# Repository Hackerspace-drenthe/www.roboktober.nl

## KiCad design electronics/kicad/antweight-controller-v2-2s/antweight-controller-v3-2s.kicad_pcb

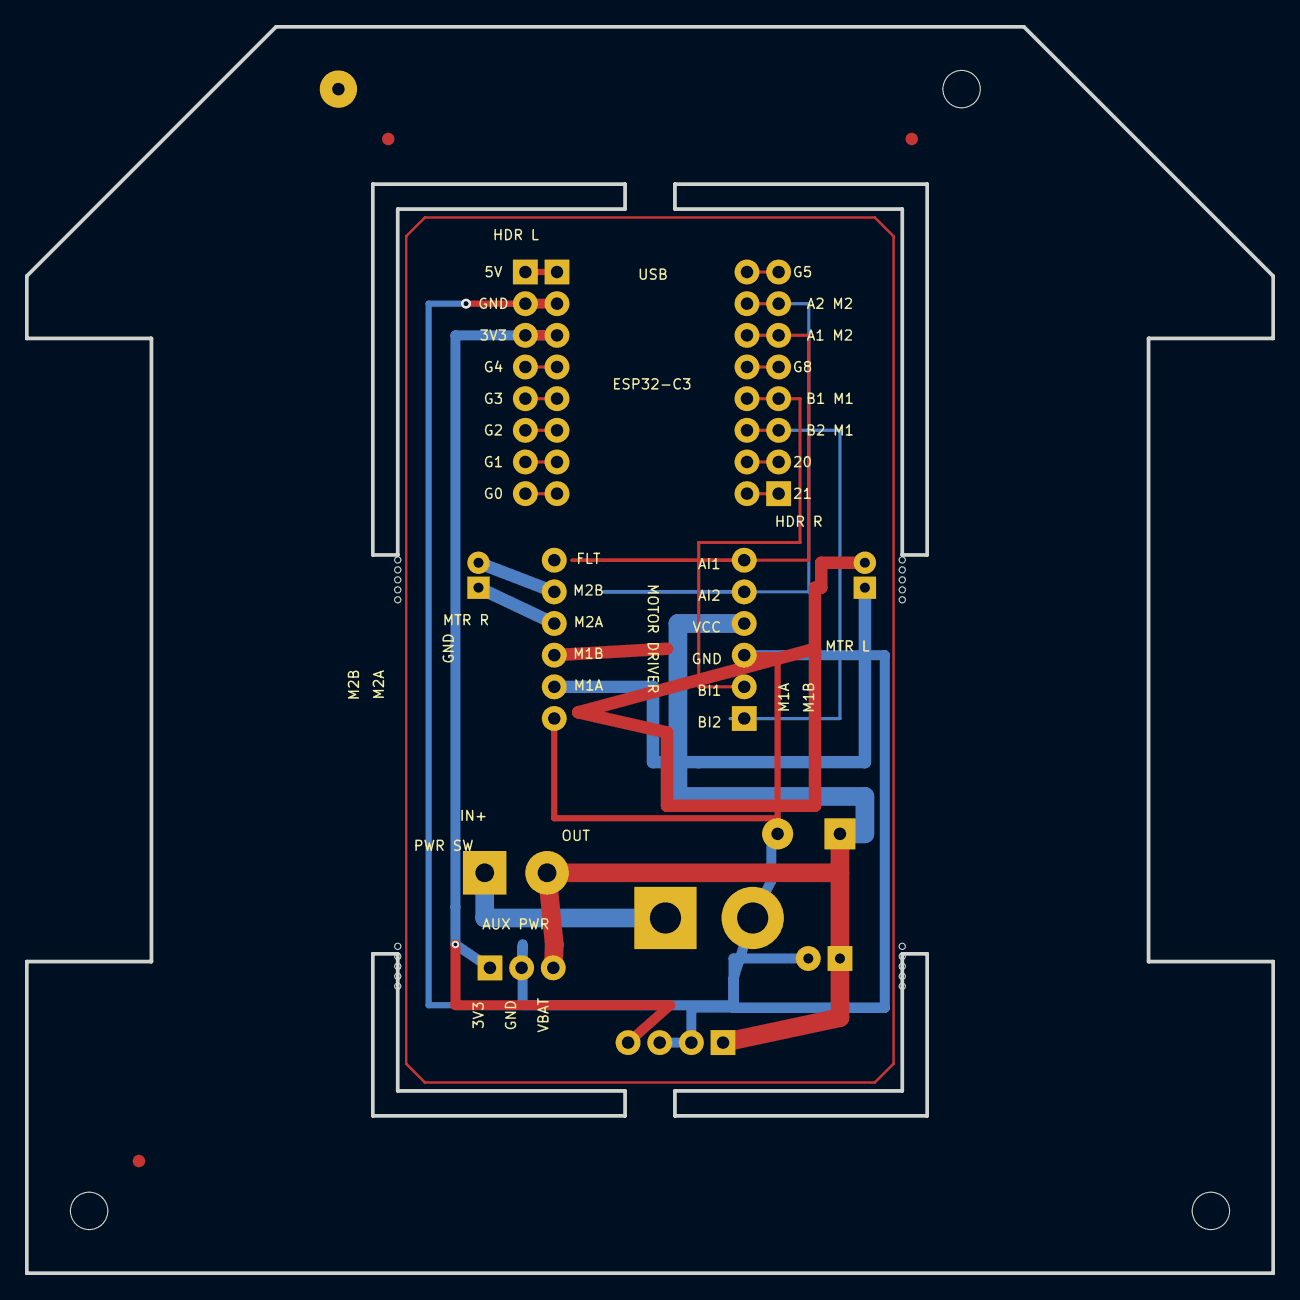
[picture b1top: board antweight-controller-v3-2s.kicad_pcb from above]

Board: 2 copper layers, 100.0 x 100.0 mm, 22 parts (0 on the bottom side), 22 nets.

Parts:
C1_C2: 100nF + 470uF/16V; CAPS_DRIVER
FD1, FD2, FD3: FIDUCIAL; FIDUCIAL_1MM
J4: FUSED 2S INPUT; BATTERY_SOLDER_PADS_5A
J5: MOTOR LEFT; JST_PH_MOTOR
J6: MOTOR RIGHT; JST_PH_MOTOR
J8: ESP32 LEFT ALL PINS; ESP32_LEFT_ALL_PINS_BREAKOUT_1X08_UNPOPULATED
J9: ESP32 RIGHT SIGNALS; ESP32_RIGHT_SIGNAL_BREAKOUT_1X08_UNPOPULATED
J10: 3V3 GND VBAT_SW; ACCESSORY_POWER_1X03_UNPOPULATED
MB3, MB4, MB5, MB6: MOUSE_BITE; MOUSE_BITE_5X0.5
SW1: MAIN POWER; SWITCH_VERIFY
TH1, TH2, TH3, TH4: TOOLING_3MM; TOOLING_HOLE_3MM
U1: ESP32-C3 SUPERMINI; ESP32_C3_MACHINED_SOCKET_VERIFY
U2: DRV8833; DRV8833_MACHINED_SOCKET_VERIFY
U3: MINI-360 MP2307DN 3V3; MINI360_MP2307DN_WIRED

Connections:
3V3: J8.3, J10.1, U1.3, U3.4
5V_NC: J8.1, U1.1
AIN1_GPIO7: J9.6, U1.14, U2.11
AIN2_GPIO6: J9.7, U1.15, U2.9
BIN1_GPIO9: J9.4, U1.12, U2.3
BIN2_GPIO10: J9.3, U1.11, U2.1
GND: C1_C2.2, J4.2, J8.2, J10.2, U1.2, U2.2, U2.5, U3.2, U3.3
GPIO0_SPARE: J8.8, U1.8
GPIO1_SPARE: J8.7, U1.7
GPIO2_SPARE: J8.6, U1.6
GPIO3_SPARE: J8.5, U1.5
GPIO4_SPARE: J8.4, U1.4
GPIO5_SPARE: J9.8, U1.16
GPIO8_LED_EXPANSION: J9.5, U1.13
GPIO20_SPARE: J9.2, U1.10
GPIO21_SPARE: J9.1, U1.9
M1A: J5.1, U2.4
M1B: J5.2, U2.6
M2A: J6.1, U2.8
M2B: J6.2, U2.10
VBAT_RAW: J4.1, SW1.1
VBAT_SW: C1_C2.1, J10.3, SW1.2, U2.7, U3.1

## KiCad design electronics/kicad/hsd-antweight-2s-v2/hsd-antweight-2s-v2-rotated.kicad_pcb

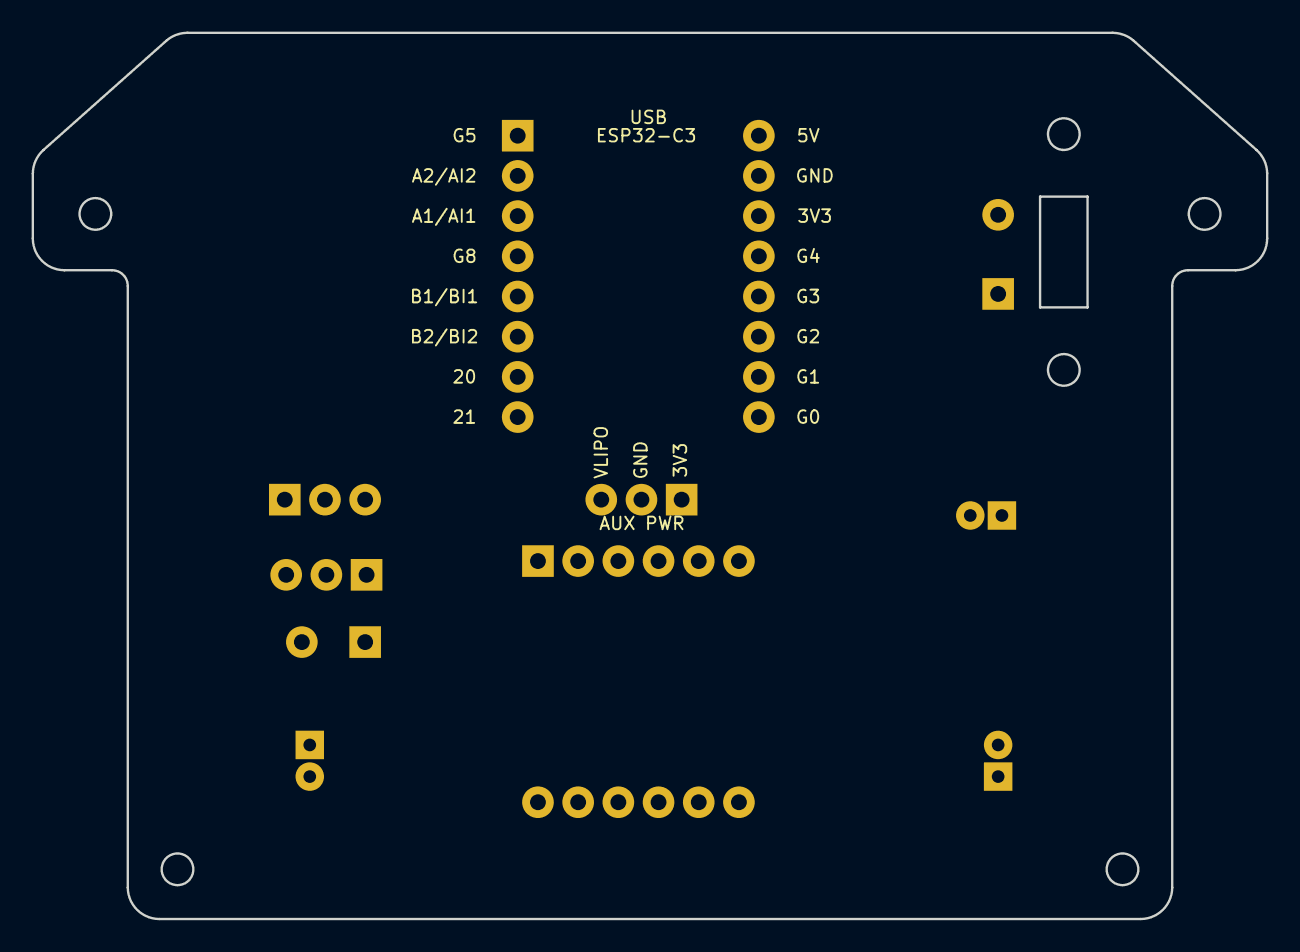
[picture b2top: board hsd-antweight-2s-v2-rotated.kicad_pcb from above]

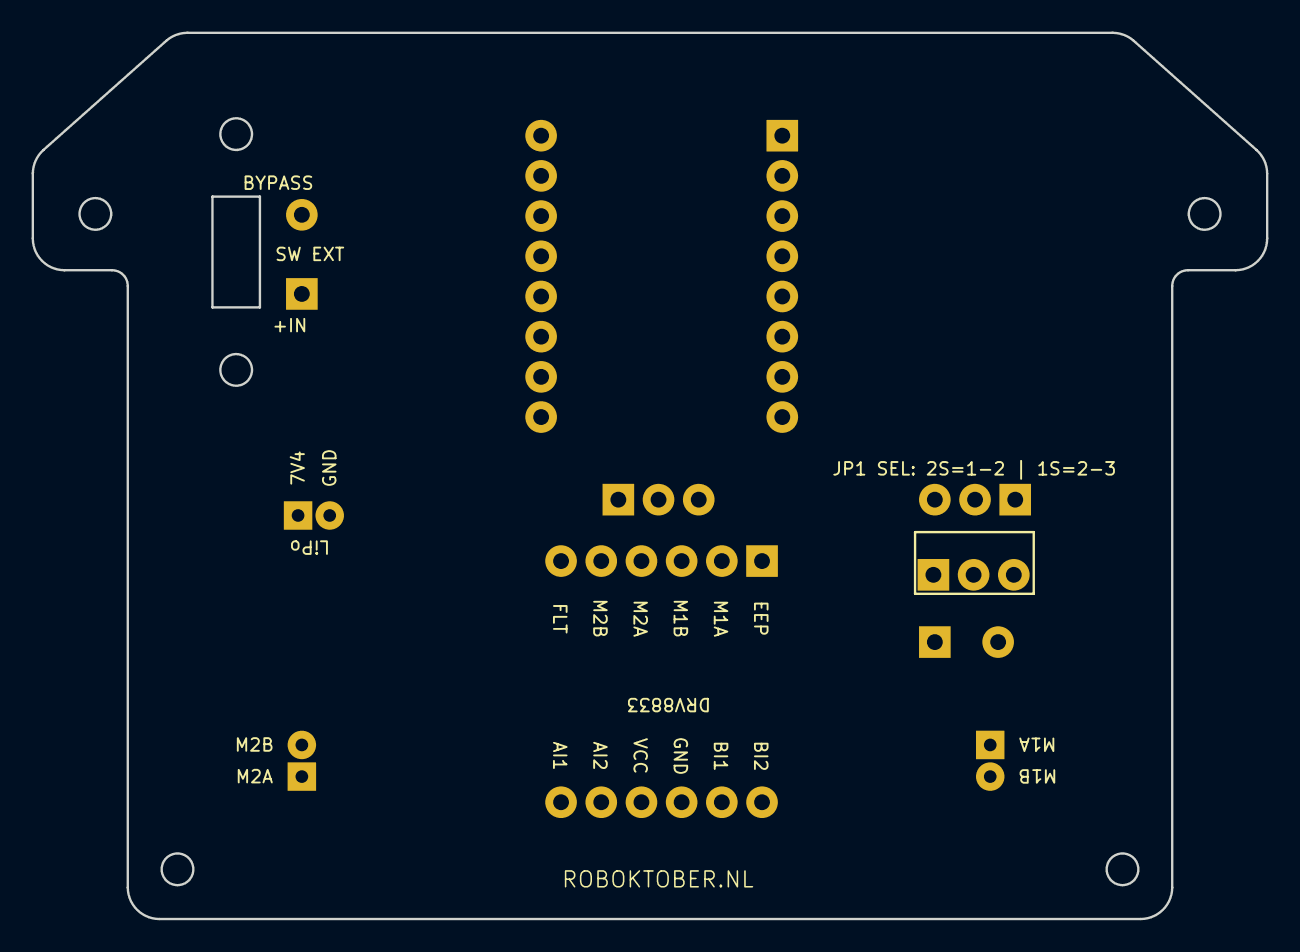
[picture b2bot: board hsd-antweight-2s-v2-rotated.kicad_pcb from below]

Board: 2 copper layers, 78.0 x 56.0 mm, 10 parts (9 on the bottom side), 13 nets, no tracks yet.

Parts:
C1_C2: DRIVER CAPS; CAPS_DRIVER
J4: BATTERY; JST_PH_BATTERY
J5: MOTOR LEFT; JST_PH_MOTOR
J6: MOTOR RIGHT; JST_PH_MOTOR
J10: 3V3 GND VLIPO; ACCESSORY_POWER_1X03_UNPOPULATED
JP1: ESP PWR SEL: REG-3V3-1S; ACCESSORY_POWER_1X03_UNPOPULATED
SW1: SW EXT VBAT_RAW/VBAT_SW; SWITCH_EXT_1X02
U1: ESP32-C3 SUPERMINI; ESP32_C3_SUPERMINI
U2: DRV8833; DRV8833_MACHINED_SOCKET_VERIFY
U3: EXT REG LOGIC VIN GND VOUT; REGULATOR_EXT_1X03

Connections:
3V3: J10.1, JP1.2, U1.14
AIN1_GPIO7: U1.3, U2.1
AIN2_GPIO6: U1.2, U2.3
BIN1_GPIO9: U1.5, U2.9
BIN2_GPIO10: U1.6, U2.11
GND: C1_C2.2, J4.2, J10.2, U1.15, U2.7, U3.2
M1A: J5.1, U2.10
M1B: J5.2, U2.8
M2A: J6.1, U2.6
M2B: J6.2, U2.4
REG_3V3_2S: JP1.1, U3.3
VBAT_RAW: J4.1, SW1.1
VBAT_SW: C1_C2.1, J10.3, JP1.3, SW1.2, U2.5, U3.1
